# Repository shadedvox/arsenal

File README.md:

# Arsenal

A 6-DOF robotic arm built around a custom STM32 motor controller, closed-loop steppers, and a distributed ROS control stack. The project moves through four stages: electronics, mechanical build, firmware/control integration, and final assembly with the end effector.

---

## Stage 1 — Voxboard (electronics)

Voxboard is a custom 4-layer PCB motor controller built to drive all six joints of the arm from a single board. It replaces an earlier ESP32 + 28BYJ-48 stepper setup with a proper closed-loop system capable of real position feedback and real-time multi-axis control.

**Core architecture**
- STM32F446RET6 (LQFP64, 180MHz Cortex-M4 with FPU) handles all real-time motor control
- Raspberry Pi 3B+ runs inverse kinematics (ikpy) and talks to the STM32 over UART
- 3x TMC2209 drivers for the NEMA17 motors at roll, pitch, and yaw
- 3x TMC5160 drivers for the NEMA23 motors at elbow, base and shoulder
- 10 to 20:1 cycloidal gearbox on every joint, with an MT6835 absolute magnetic encoder at each gearbox output shaft for true closed-loop position feedback, no homing required on power-up

**Connectivity**
- CAN (for the end-effector node), USB, dual SPI (encoders + TMC5160s), triple UART (TMC2209s + RPi), I2C, SWD for debug

**Power**
- Single 24V input via XT60, reverse-polarity and surge protected, stepped down to 5V (buck) and 3.3V (LDO) for logic
- USB VBUS backup path with ideal-diode OR-ing, so the board can run off USB power alone for debug/bring-up

**Project Files & Schematics :** [\Stage1 - STM\voxboard](https://github.com/shadedvox/arsenal/tree/main/Stage1%20-%20STM/voxboard)

**Status: design completed - fabrication pending**

---

## Stage 2 — Mechanical build

3D-printed cycloidal gearboxes and joint assemblies, structural frame for the arm.

**Status: in progress**

---

## Stage 3 — Firmware & control

Real-time motor control on the STM32, distributed ROS architecture with MoveIt running on the Pi/PC side.

**Status: in progress**

---

## Stage 4 — Integration & end effector

Final assembly, end-effector design, and full-arm bring-up.

**Status: in progress**

---

*© 2026 Atharva Chauhan, Vox*

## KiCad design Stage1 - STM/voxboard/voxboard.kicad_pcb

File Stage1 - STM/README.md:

# Voxboard

A custom 4-layer motor controller board for a 6-DOF robotic arm, built around an STM32F446RET6. It drives six stepper motors with closed-loop magnetic encoder feedback, talks to a Raspberry Pi for inverse kinematics, and exposes CAN, I2C, and USB for future expansion.

---

## Core MCU

- STM32F446RET6, Cortex-M4 running at 180MHz off an 8MHz crystal
- Standard ST decoupling scheme on VDD/VBAT and VDDA, per-pin 100nF caps plus bulk capacitors
- NRST push button (internal pull-up, no external needed) and a BOOT0 slide switch
- 5-pin SWD header for programming via ST-Link
- Heartbeat LED for status indication

---

## Power

24V enters through an XT60 connector and feeds a back-EMF and filtering network before splitting off to the motors directly. A buck converter (TPS54331) steps 24V down to 5V, feeding an LDO that regulates the final 3.3V logic rail. Running two stages instead of a single 24V-to-3.3V converter keeps the logic rail clean and low-noise.

A P-MOSFET and Schottky diode pair handles priority between the buck output and USB VBUS, so the board always runs off the battery when it's present and only falls back to USB power for programming when it isn't.

Status LEDs indicate activity on each rail: red for 24V, yellow for VBUS/5V, yellow-green for 3.3V.

---

## Motor drivers

Six motors in total: three NEMA17s (roll, pitch, yaw) driven by TMC2209s over single-wire half-duplex UART, and three NEMA23s (base, shoulder, elbow) driven by TMC5160s over a shared SPI bus. The NEMA23s sit at the joints carrying the highest load.

Each TMC2209 gets an address set through its MS1/MS2 pins, allowing multiple drivers to share one UART line. STEP, DIR, and EN are wired per driver, with series resistors for current limiting. DIAG is only connected on the TMC5160s, since those joints need it most and GPIO budget is tight.

Motors connect through JST-XH connectors mounted directly on the board.

---

## Encoders

Six MT6835 magnetic encoders, one per joint, provide absolute position feedback at the gearbox output shaft. They share a single SPI bus. CAL_EN is tied to ground since calibration is triggered through software instead.

---

## CAN bus

An SN65HVD230DR transceiver gives the board a CAN interface, mainly intended for connecting an end-effector controller later on. Includes end-termination and ESD protection placed right at the connector.

---

## I2C

A couple of JST-GH connectors broken out for I2C, left open for future sensors. Same ESD protection approach as the rest of the board's external connectors.

---

## USB

A USB-C 2.0 connector with ESD protection on the D+/D- lines, used purely for programming and debug, not for powering the whole system under normal operation.

---

## ESD protection

Connectors that reach off-board (USB-C, CAN, RPi UART, I2C) get ESD protection right at the connector, stopping any transient before it reaches the rest of the circuit. Buses that stay entirely on-board (encoder SPI, driver SPI, TMC2209 UART) get their ESD protection near the MCU instead, guarding the chip pins directly.

---

## Layout and routing

4-layer stackup: signal, ground, 3.3V power, signal. The ground plane is a single unified pour, motors and logic share it, with noise managed through tight decoupling and via stitching rather than a split plane.

High-current traces run as fill zones rather than individually routed tracks, since a shaped pour handles current distribution far more cleanly for the 24V rail. All vias are standard through-hole, 0.4/0.3mm, chosen as JLCPCB's smallest reliably manufacturable size.

Ground stitching vias run alongside every high-speed signal via to keep return paths short and reduce EMI.

---

## Final board

Custom 3D models were made in Fusion 360 for parts without existing KiCad models, including the main inductor and the motor driver modules. Silkscreen on the back carries a short board description, designer credit, and a small logo.

---

## BOM

Parts list exported from KiCad and matched to JLCPCB part numbers. Total parts cost as of October 2026: **$263.61 for 2 PCBAs** (excludes PCB fabrication and assembly charges). Full BOM and schematic files live in [`/Stage1 - STM`](https://github.com/shadedvox/arsenal/tree/main/Stage1%20-%20STM).

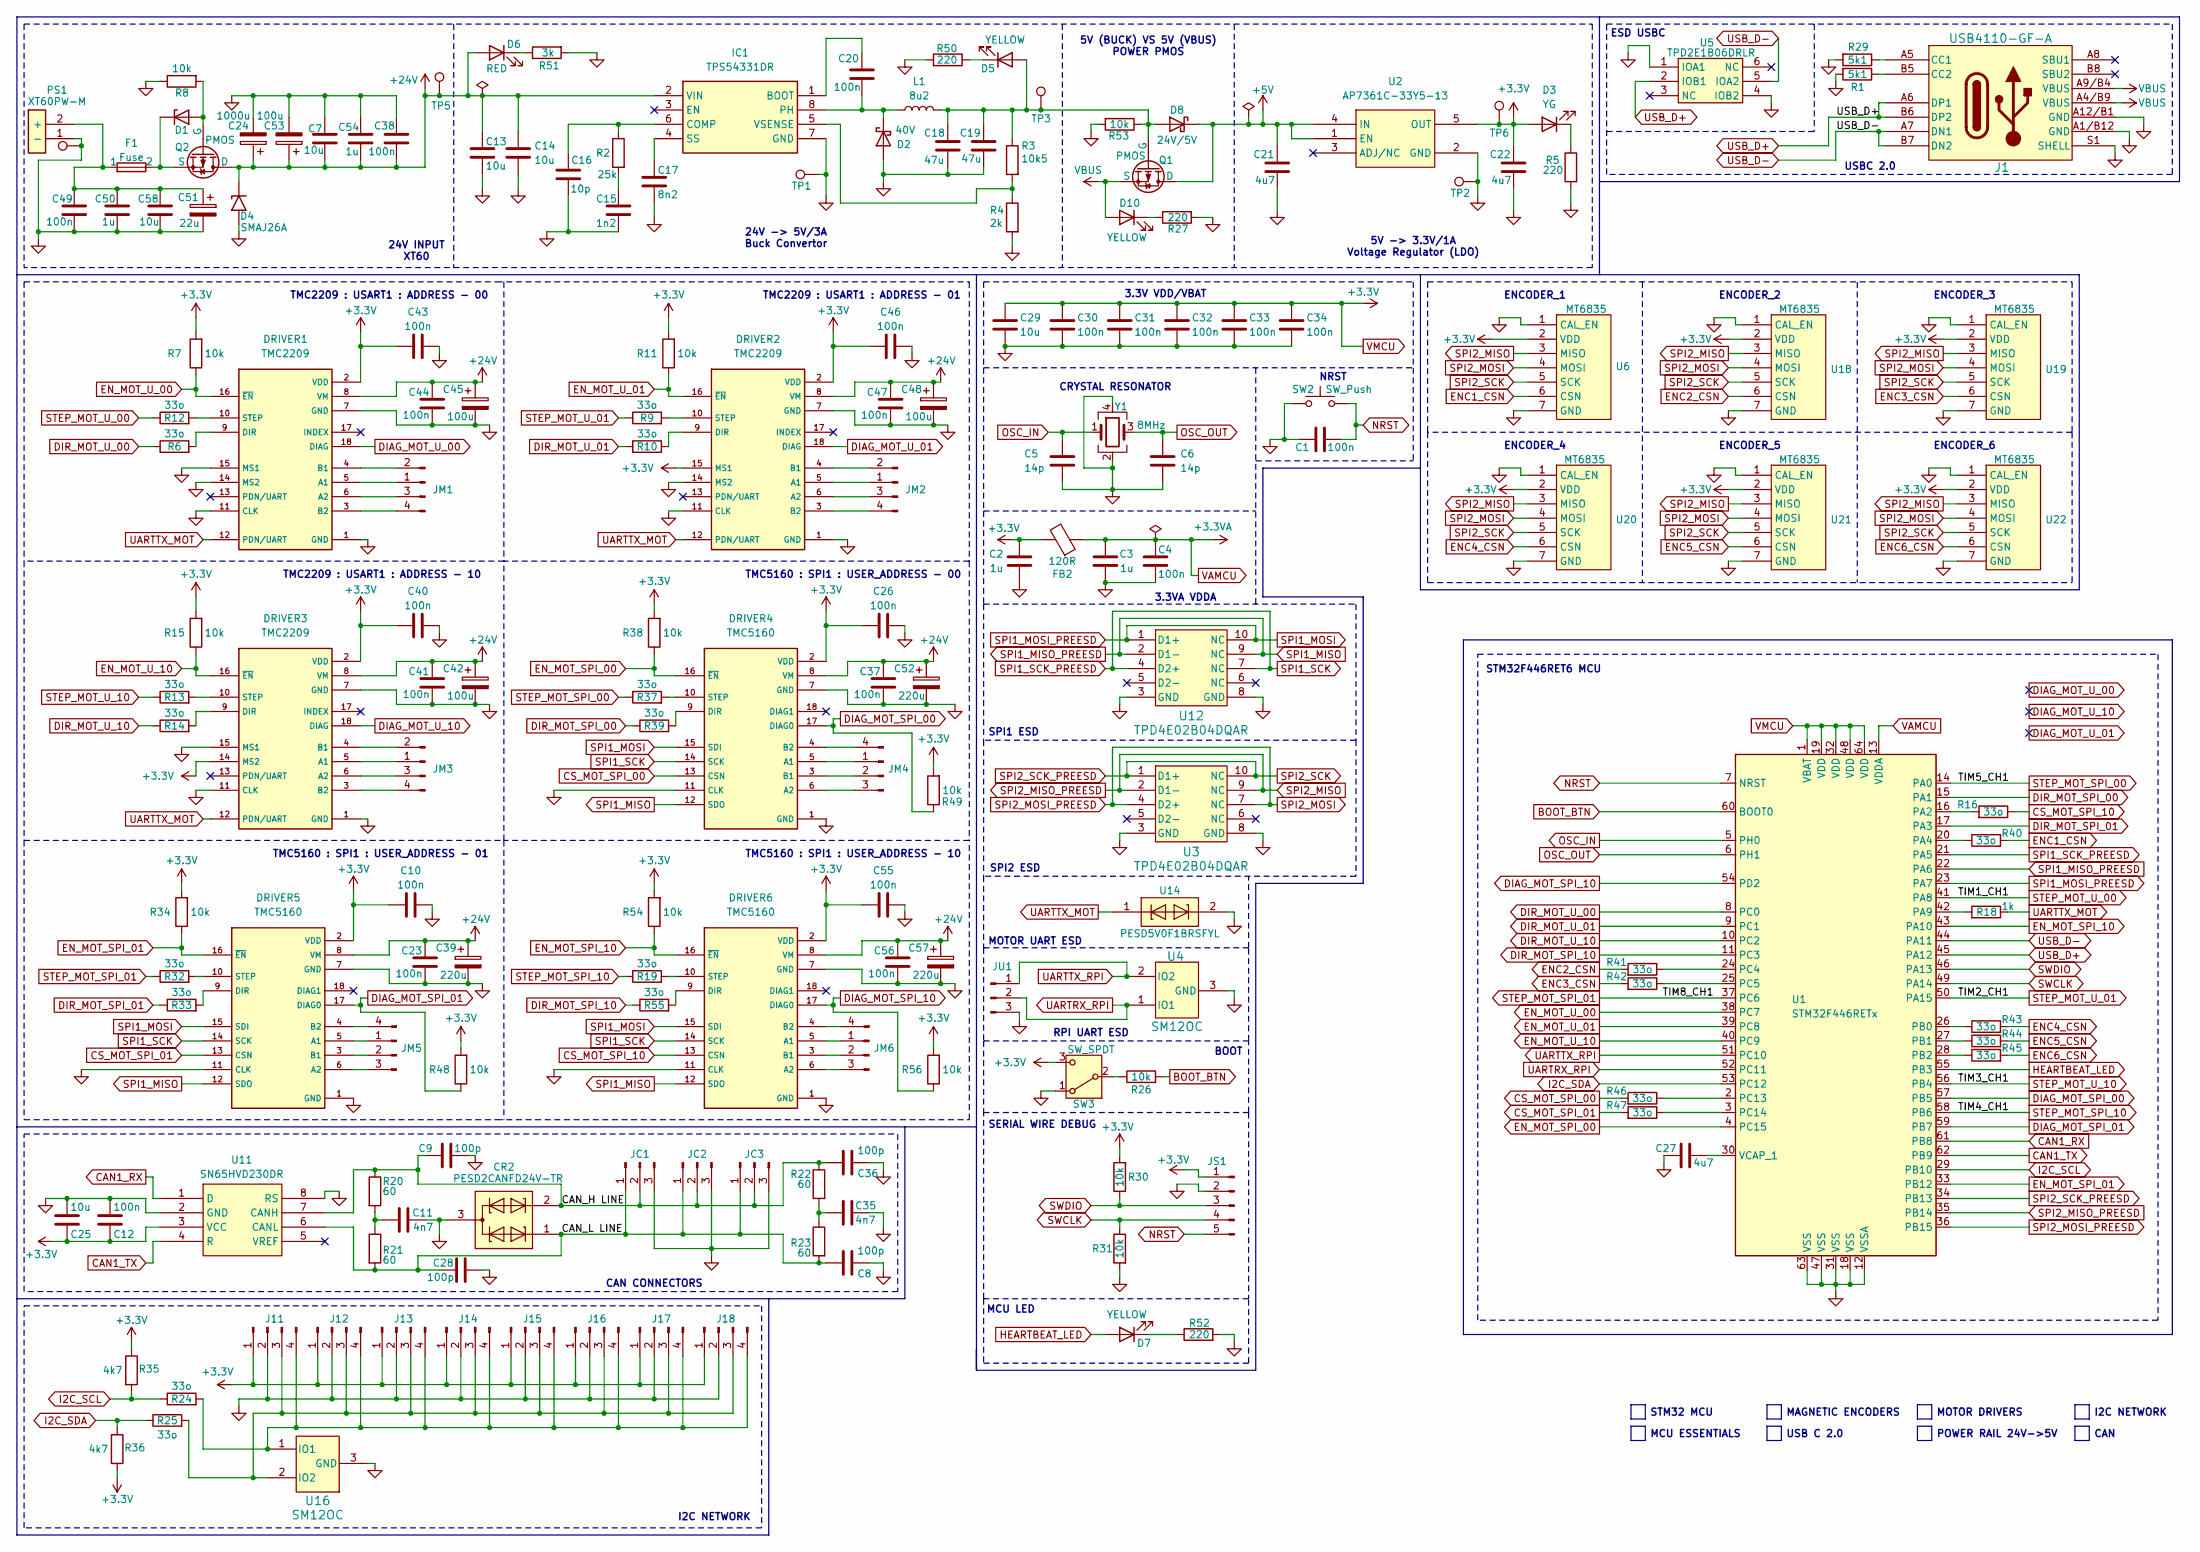
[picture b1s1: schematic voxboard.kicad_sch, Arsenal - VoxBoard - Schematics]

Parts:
C1, C4, C10, C12, C23, C26, C30, C31, C32, C33, C34, C37, C38, C40, C41, C43, C44, C46, C47, C49, C55, C56: 100n; C_0402_1005Metric
C2, C3, C50, C54: 1u; C_0603_1608Metric
C5, C6: 14p; C_0402_1005Metric
C7, C25, C29, C58: 10u; C_0805_2012Metric
C8, C9, C28, C36: 100p; C_0402_1005Metric
C11, C35: 4n7; C_0402_1005Metric
C13, C14: 10u; C_1210_3225Metric
C15: 1n2; C_0805_2012Metric
C16: 10p; C_0805_2012Metric
C17: 8n2; C_0201_0603Metric
C18, C19: 47u; C_1210_3225Metric
C20: 100n; C_0805_2012Metric
C21, C22, C27: 4u7; C_0603_1608Metric
C24: 1000u; CP_Radial_D12.5mm_P5.00mm
C39, C52, C57: 220u; CP_Radial_D10.0mm_P5.00mm
C42, C45, C48: 100u; CP_Radial_D8.0mm_P3.50mm
C51: 22u; CP_Radial_D5.0mm_P2.00mm
C53: 100u; CP_Radial_D6.3mm_P2.50mm
CR2: PESD2CANFD24V-TR; SOT-23
D1: D_Zener; D_SOD-123
D2: 40V; D_SMC
D3: YG; LED_0603_1608Metric
D4: SMAJ26A; D_SMA
D5, D10: YELLOW; LED_0603_1608Metric
D6: RED; LED_0603_1608Metric
D7: YELLOW; LED_0805_2012Metric
D8: 24V/5V; SOT-23
DRIVER1, DRIVER2, DRIVER3: TMC2209; MODULE_TMC2209_5160
DRIVER4, DRIVER5, DRIVER6: TMC5160; MODULE_TMC2209_5160
F1: Fuse; CONN_3557-2_KEY
FB2: 120R; L_0603_1608Metric
IC1: TPS54331DR; SOIC-8_3.9x4.9mm_P1.27mm
J1: USB4110-GF-A; USB_C_Receptacle_GCT_USB4110
J11, J12, J13, J14, J15, J16, J17, J18: Conn_01x04_Pin; JST_GH_BM04B-GHS-TBT_1x04-1MP_P1.25mm_Vertical
JC1, JC2, JC3: Conn_01x03_Pin; JST_GH_BM03B-GHS-TBT_1x03-1MP_P1.25mm_Vertical
JM1, JM2, JM3, JM4, JM5, JM6: Conn_01x04_Pin; JST_XA_B04B-XASK-1_1x04_P2.50mm_Vertical
JS1: Conn_01x05_Pin; PinHeader_1x05_P2.54mm_Vertical
JU1: Conn_01x03_Pin; PinHeader_1x03_P2.54mm_Vertical
L1: 8u2; L_KOHERELEC_MDA7050_7.3x6.6mm
PS1: XT60PW-M; AMASS_XT60PW-M_1x02_P7.20mm_Horizontal
Q1: PMOS; SOT-23
Q2: PMOS; TO-252-2
R1, R29: 5k1; R_0402_1005Metric
R2: 25k; R_0603_1608Metric
R3: 10k5; R_0402_1005Metric
R4: 2k; R_0402_1005Metric
R5, R27, R50, R52: 220; R_0402_1005Metric
R6, R9, R10, R12, R13, R14, R16, R19, R24, R25, R32, R33, R37, R39, R40, R41, R42, R43, R44, R45, R46, R47, R55: 33o; R_0402_1005Metric
R7, R8, R11, R15, R26, R30, R31, R34, R38, R48, R49, R53, R54, R56: 10k; R_0402_1005Metric
R18: 1k; R_0402_1005Metric
R20, R21, R22, R23: 60; R_0603_1608Metric
R35, R36: 4k7; R_0402_1005Metric
R51: 3k; R_0402_1005Metric
SW2: SW_Push; SW_PUSH_B3U-1000PM
SW3: SW_SPDT; SW_SPDT_PCM12
TP1, TP2, TP4: TestPoint; TestPoint_Pad_2.0x2.0mm
TP3, TP5, TP6: TestPoint; TestPoint_Pad_D2.0mm
U1: STM32F446RETx; LQFP64-10x10mm
U2: AP7361C-33Y5-13; AP7361C-33Y5-13_SOT89-5_DIO
U3, U12: TPD4E02B04DQAR; USON-10_2.5x1.0mm_P0.5mm
U4, U16: SM12OC; SOT-23
U5: TPD2E1B06DRLR; SOT-666
U6, U18, U19, U20, U21, U22: MT6835; JST_GH_BM07B-GHS-TBT_1x07-1MP_P1.25mm_Vertical
U11: SN65HVD230DR; SOIC-8_3.9x4.9mm_P1.27mm
U14: PESD5V0F1BRSFYL; Nexperia_DSN0603-2_0.6x0.3mm_P0.4mm
Y1: 8MHz; Crystal_SMD_3225-4Pin_3.2x2.5mm

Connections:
+5V: C21.1, D8.1 (K), Q1.1 (D), U2.1 (EN), U2.4 (IN)
+24V: C7.2, C13.1, C14.1, C23.1, C24.1, C37.1, C38.2, C39.1, C41.1, C42.1, C44.1, C45.1, C47.1, C48.1, C52.1, C53.1, C54.2, C56.1, C57.1, D4.1 (A1), D6.2 (A), DRIVER1.8 (VM), DRIVER2.8 (VM), DRIVER3.8 (VM), DRIVER4.8 (VM), DRIVER5.8 (VM), DRIVER6.8 (VM), IC1.2 (VIN), Q2.1 (D), TP5.1
/CAN_H LINE: C9.1, C36.1, CR2.2, JC1.2, JC2.2, JC3.2, R20.1, R22.1, U11.7 (CANH)
/CAN_L LINE: C8.1, C28.1, CR2.1, JC1.1, JC2.1, JC3.1, R21.2, R23.2, U11.6 (CANL)
BOOT_BTN: R26.2, U1.60 (BOOT0)
CAN1_RX: U1.61 (PB8), U11.1 (D)
CAN1_TX: U1.62 (PB9), U11.4 (R)
CS_MOT_SPI_00: DRIVER4.13 (CSN), R46.2
CS_MOT_SPI_01: DRIVER5.13 (CSN), R47.2
CS_MOT_SPI_10: DRIVER6.13 (CSN), R16.1
DIAG_MOT_SPI_00: DRIVER4.17 (DIAG0), R49.1, U1.57 (PB5)
DIAG_MOT_SPI_01: DRIVER5.17 (DIAG0), R48.1, U1.59 (PB7)
DIAG_MOT_SPI_10: DRIVER6.17 (DIAG0), R56.1, U1.54 (PD2)
DIAG_MOT_U_00: DRIVER1.18 (DIAG)
DIAG_MOT_U_01: DRIVER2.18 (DIAG)
DIAG_MOT_U_10: DRIVER3.18 (DIAG)
DIR_MOT_SPI_00: R39.1, U1.15 (PA1)
DIR_MOT_SPI_01: R33.1, U1.17 (PA3)
DIR_MOT_SPI_10: R55.1, U1.11 (PC3)
DIR_MOT_U_00: R6.1, U1.8 (PC0)
DIR_MOT_U_01: R10.1, U1.9 (PC1)
DIR_MOT_U_10: R14.1, U1.10 (PC2)
ENC1_CSN: R40.2, U6.6 (CSN)
ENC2_CSN: R41.2, U18.6 (CSN)
ENC3_CSN: R42.2, U19.6 (CSN)
ENC4_CSN: R43.2, U20.6 (CSN)
ENC5_CSN: R44.2, U21.6 (CSN)
ENC6_CSN: R45.2, U22.6 (CSN)
EN_MOT_SPI_00: DRIVER4.16 (~EN), R38.1, U1.4 (PC15)
EN_MOT_SPI_01: DRIVER5.16 (~EN), R34.1, U1.33 (PB12)
EN_MOT_SPI_10: DRIVER6.16 (~EN), R54.1, U1.43 (PA10)
EN_MOT_U_00: DRIVER1.16 (~EN), R7.1, U1.38 (PC7)
EN_MOT_U_01: DRIVER2.16 (~EN), R11.1, U1.39 (PC8)
EN_MOT_U_10: DRIVER3.16 (~EN), R15.1, U1.40 (PC9)
GND: C1.1, C2.2, C3.2, C4.2, C5.2, C6.2, C7.1, C8.2, C9.2, C10.2, C11.2, C12.2, C13.2, C14.2, C15.2, C16.2, C17.2, C18.2, C19.2, C21.2, C22.2, C23.2, C24.2, C25.2, C26.2, C27.1, C28.2, C29.2, C30.2, C31.2, C32.2, C33.2, C34.2, C35.2, C36.2, C37.2, C38.1, C39.2, C40.2, C41.2, C42.2, C43.2, C44.2, C45.2, C46.2, C47.2, C48.2, C49.2, C50.2, C51.2, C52.2, C53.2, C54.1, C55.2, C56.2, C57.2, C58.2, CR2.3, D2.2 (A), D4.2 (A2), DRIVER1.1 (GND), DRIVER1.7 (GND), DRIVER1.11 (CLK), DRIVER1.14 (MS2), DRIVER1.15 (MS1), DRIVER2.1 (GND), DRIVER2.7 (GND), DRIVER2.11 (CLK), DRIVER2.14 (MS2), DRIVER3.1 (GND), DRIVER3.7 (GND), DRIVER3.11 (CLK), DRIVER3.15 (MS1), DRIVER4.1 (GND), DRIVER4.7 (GND), DRIVER4.11 (CLK), DRIVER5.1 (GND), DRIVER5.7 (GND), DRIVER5.11 (CLK), DRIVER6.1 (GND), DRIVER6.7 (GND), DRIVER6.11 (CLK), IC1.7 (GND), J1.A1/B12 (GND), J1.A12/B1 (GND), J1.S1 (SHELL), J11.2, J12.2, J13.2, J14.2, J15.2, J16.2, J17.2, J18.2, JC1.3, JC2.3, JC3.3, JS1.2, JU1.3, PS1.1 (-), R1.2, R4.2, R5.2, R8.1, R27.2, R29.2, R31.2, R50.2, R51.2, R52.2, R53.2, SW2.1, SW3.1 (A), TP1.1, TP2.1, TP4.1, U1.12 (VSSA), U1.18 (VSS), U1.31 (VSS), U1.47 (VSS), U1.63 (VSS), U2.2 (GND), U3.3 (GND), U3.8 (GND), U4.3 (GND), U5.1 (IOA1), U5.4 (IOB2), U6.1 (CAL_EN), U6.7 (GND), U11.2 (GND), U11.8 (RS), U12.3 (GND), U12.8 (GND), U14.2, U16.3 (GND), U18.1 (CAL_EN), U18.7 (GND), U19.1 (CAL_EN), U19.7 (GND), U20.1 (CAL_EN), U20.7 (GND), U21.1 (CAL_EN), U21.7 (GND), U22.1 (CAL_EN), U22.7 (GND), Y1.2 (G), Y1.4 (G)
HEARTBEAT_LED: D7.2 (A), U1.55 (PB3)
I2C_SCL: R24.1, R35.2, U1.29 (PB10)
I2C_SDA: R25.1, R36.1, U1.53 (PC12)
NRST: C1.2, JS1.5, SW2.2, U1.7 (NRST)
unnamed: C11.1, R20.2, R21.1
unnamed: C15.1, R2.2
unnamed: C35.1, R22.2, R23.1
unnamed: D1.2 (A), Q2.2 (G), R8.2
unnamed: D1.1 (K), F1.2, Q2.3 (S)
unnamed: C20.2, D2.1 (K), IC1.8 (PH), L1.1
unnamed: D3.1 (K), R5.1
unnamed: C18.1, C19.1, D5.2 (A), D8.2 (A), L1.2, Q1.2 (G), R3.1, R53.1, TP3.1
unnamed: D5.1 (K), R50.1
unnamed: D6.1 (K), R51.1
unnamed: D7.1 (K), R52.1
unnamed: D10.1 (K), R27.1
unnamed: DRIVER1.5 (A1), JM1.1
unnamed: DRIVER1.6 (A2), JM1.3
unnamed: DRIVER1.4 (B1), JM1.2
unnamed: DRIVER1.3 (B2), JM1.4
unnamed: DRIVER1.9 (DIR), R6.2
unnamed: DRIVER1.10 (STEP), R12.2
unnamed: DRIVER2.5 (A1), JM2.1
unnamed: DRIVER2.6 (A2), JM2.3
unnamed: DRIVER2.4 (B1), JM2.2
unnamed: DRIVER2.3 (B2), JM2.4
unnamed: DRIVER2.9 (DIR), R10.2
unnamed: DRIVER2.10 (STEP), R9.2
unnamed: DRIVER3.5 (A1), JM3.1
unnamed: DRIVER3.6 (A2), JM3.3
unnamed: DRIVER3.4 (B1), JM3.2
unnamed: DRIVER3.3 (B2), JM3.4
unnamed: DRIVER3.9 (DIR), R14.2
unnamed: DRIVER3.10 (STEP), R13.2
unnamed: DRIVER4.5 (A1), JM4.1
unnamed: DRIVER4.6 (A2), JM4.3
unnamed: DRIVER4.3 (B1), JM4.2
unnamed: DRIVER4.4 (B2), JM4.4
unnamed: DRIVER4.9 (DIR), R39.2
unnamed: DRIVER4.10 (STEP), R37.2
unnamed: DRIVER5.5 (A1), JM5.1
unnamed: DRIVER5.6 (A2), JM5.3
unnamed: DRIVER5.3 (B1), JM5.2
unnamed: DRIVER5.4 (B2), JM5.4
unnamed: DRIVER5.9 (DIR), R33.2
unnamed: DRIVER5.10 (STEP), R32.2
unnamed: DRIVER6.5 (A1), JM6.1
unnamed: DRIVER6.6 (A2), JM6.3
unnamed: DRIVER6.3 (B1), JM6.2
unnamed: DRIVER6.4 (B2), JM6.4
unnamed: DRIVER6.9 (DIR), R55.2
unnamed: DRIVER6.10 (STEP), R19.2
unnamed: C20.1, IC1.1 (BOOT)
unnamed: C16.1, IC1.6 (COMP), R2.1
unnamed: C17.1, IC1.4 (SS)
unnamed: IC1.5 (VSENSE), R3.2, R4.1
unnamed: J1.A5 (CC1), R29.1
unnamed: J1.B5 (CC2), R1.1
unnamed: J11.3, J12.3, J13.3, J14.3, J15.3, J16.3, J17.3, J18.3, R25.2, U16.2 (IO2)
unnamed: J11.4, J12.4, J13.4, J14.4, J15.4, J16.4, J17.4, J18.4, R24.2, U16.1 (IO1)
unnamed: C49.1, C50.1, C51.1, C58.1, F1.1, PS1.2 (+)
unnamed: R26.1, SW3.2 (B)
unnamed: R16.2, U1.16 (PA2)
unnamed: R40.1, U1.20 (PA4)
unnamed: R18.2, U1.42 (PA9)
unnamed: R43.1, U1.26 (PB0)
unnamed: R44.1, U1.27 (PB1)
unnamed: R45.1, U1.28 (PB2)
unnamed: R41.1, U1.24 (PC4)
unnamed: R42.1, U1.25 (PC5)
unnamed: R46.1, U1.2 (PC13)
unnamed: R47.1, U1.3 (PC14)
unnamed: C27.2, U1.30 (VCAP_1)
OSC_IN: C5.1, U1.5 (PH0), Y1.1
OSC_OUT: C6.1, U1.6 (PH1), Y1.3
SPI1_MISO: DRIVER4.12 (SDO), DRIVER5.12 (SDO), DRIVER6.12 (SDO), U1.22 (PA6), U12.2 (D1-), U12.9 (NC)
SPI1_MOSI: DRIVER4.15 (SDI), DRIVER5.15 (SDI), DRIVER6.15 (SDI), U1.23 (PA7), U12.1 (D1+), U12.10 (NC)
SPI1_SCK: DRIVER4.14 (SCK), DRIVER5.14 (SCK), DRIVER6.14 (SCK), U1.21 (PA5), U12.4 (D2+), U12.7 (NC)
SPI2_MISO: U1.35 (PB14), U3.2 (D1-), U3.9 (NC), U6.3 (MISO), U18.3 (MISO), U19.3 (MISO), U20.3 (MISO), U21.3 (MISO), U22.3 (MISO)
SPI2_MOSI: U1.36 (PB15), U3.4 (D2+), U3.7 (NC), U6.4 (MOSI), U18.4 (MOSI), U19.4 (MOSI), U20.4 (MOSI), U21.4 (MOSI), U22.4 (MOSI)
SPI2_SCK: U1.34 (PB13), U3.1 (D1+), U3.10 (NC), U6.5 (SCK), U18.5 (SCK), U19.5 (SCK), U20.5 (SCK), U21.5 (SCK), U22.5 (SCK)
STEP_MOT_SPI_00: R37.1, U1.14 (PA0)
STEP_MOT_SPI_01: R32.1, U1.37 (PC6)
STEP_MOT_SPI_10: R19.1, U1.58 (PB6)
STEP_MOT_U_00: R12.1, U1.41 (PA8)
STEP_MOT_U_01: R9.1, U1.50 (PA15)
STEP_MOT_U_10: R13.1, U1.56 (PB4)
SWCLK: JS1.4, R31.1, U1.49 (PA14)
SWDIO: JS1.3, R30.1, U1.46 (PA13)
UARTRX_RPI: JU1.2, U1.52 (PC11), U4.1 (IO1)
UARTTX_MOT: DRIVER1.12 (PDN/UART), DRIVER2.12 (PDN/UART), DRIVER3.12 (PDN/UART), R18.1, U14.1
UARTTX_RPI: JU1.1, U1.51 (PC10), U4.2 (IO2)
USB_D+: J1.A6 (DP1), J1.B6 (DP2), U1.45 (PA12), U5.2 (IOB1)
USB_D-: J1.A7 (DN1), J1.B7 (DN2), U1.44 (PA11), U5.5 (IOA2)
VAMCU: C3.1, C4.1, FB2.1, U1.13 (VDDA)
VBUS: D10.2 (A), J1.A4/B9 (VBUS), J1.A9/B4 (VBUS), Q1.3 (S)
VMCU: C2.1, C10.1, C12.1, C22.1, C25.1, C26.1, C29.1, C30.1, C31.1, C32.1, C33.1, C34.1, C40.1, C43.1, C46.1, C55.1, D3.2 (A), DRIVER1.2 (VDD), DRIVER2.2 (VDD), DRIVER2.15 (MS1), DRIVER3.2 (VDD), DRIVER3.14 (MS2), DRIVER4.2 (VDD), DRIVER5.2 (VDD), DRIVER6.2 (VDD), FB2.2, J11.1, J12.1, J13.1, J14.1, J15.1, J16.1, J17.1, J18.1, JS1.1, R7.2, R11.2, R15.2, R30.2, R34.2, R35.1, R36.2, R38.2, R48.2, R49.2, R54.2, R56.2, SW3.3 (C), TP6.1, U1.1 (VBAT), U1.19 (VDD), U1.32 (VDD), U1.48 (VDD), U1.64 (VDD), U2.5 (OUT), U6.2 (VDD), U11.3 (VCC), U18.2 (VDD), U19.2 (VDD), U20.2 (VDD), U21.2 (VDD), U22.2 (VDD)

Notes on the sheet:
ESD USBC
TMC5160 : SPI1 : USER_ADDRESS - 10
STM32 MCU
NRST
TMC5160 : SPI1 : USER_ADDRESS - 01
ENCODER_4
MOTOR UART ESD
TMC2209 : USART1 : ADDRESS - 10
TMC2209 : USART1 : ADDRESS - 01
ENCODER_6
MOTOR DRIVERS
BOOT
MAGNETIC ENCODERS
RPI UART ESD
3.3V VDD/VBAT
CAN
TMC5160 : SPI1 : USER_ADDRESS - 00
ENCODER_5
CAN CONNECTORS
SPI1 ESD
USBC 2.0
I2C NETWORK
MCU ESSENTIALS
3.3VA VDDA
ENCODER_2
24V -> 5V/3A Buck Convertor
SPI2 ESD
ENCODER_3
USB C 2.0
MCU LED
POWER RAIL 24V->5V
CRYSTAL RESONATOR
SERIAL WIRE DEBUG
STM32F446RET6 MCU
5V -> 3.3V/1A Voltage Regulator (LDO)
TMC2209 : USART1 : ADDRESS - 00
24V INPUT XT60
ENCODER_1
5V (BUCK) VS 5V (VBUS) POWER PMOS

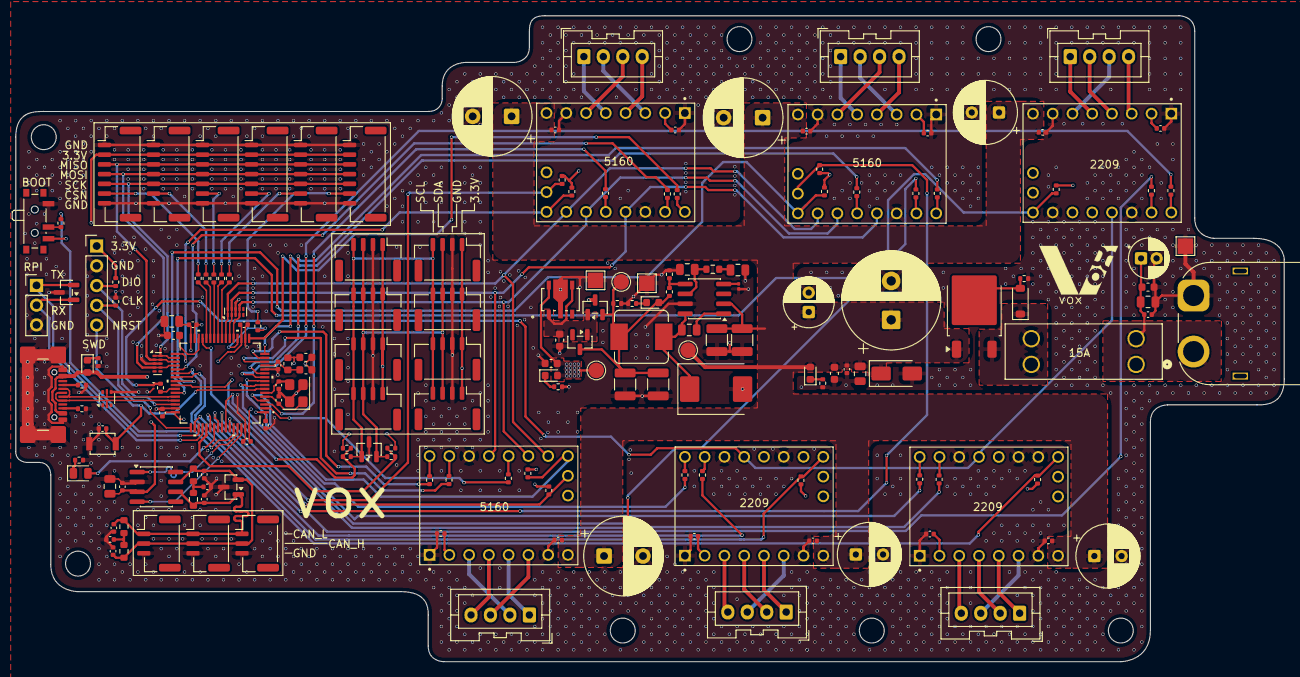
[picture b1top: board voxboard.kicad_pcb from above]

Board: 4 copper layers, 163.0 x 83.0 mm, 179 parts (0 on the bottom side), 129 nets.

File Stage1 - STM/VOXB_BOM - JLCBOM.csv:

Comment,Designator,Footprint,JLCPCB Part#(optional)
100nF,"C1, C10, C12, C23, C26, C30, C31, C32, C33, C34, C37, C38, C4, C40, C41, C43, C44, C46, C47, C49, C55, C56",C0402,C56392
4.7nF,"C11, C35",C0402,C1538
10uF,"C13, C14",C1210,C39232
1.2nF,C15,C0805,C1714
10pF,C16,C0805,C107107
8.2nF,C17,C0201,C2168104
47uF,"C18, C19",C1210,C84494
1uF,"C2, C3, C50, C54",C0603,C29936
100nF,C20,C0805,C1711
4.7uF,"C21, C22, C27",C0603,C69335
1000uF,C24,CP_Radial_D12.5mm_P5.00mm,C165529
10uF,"C25, C29, C58, C7",C0805,C440198
100pF,"C28, C36, C8, C9",C0402,C1546
220uF,"C39, C52, C57",CP_Radial_D10.0mm_P5.00mm,C19270689
100uF,"C42, C45, C48, C53",CP_Radial_D6.3mm_P2.50mm,C19270686
14pF,"C5, C6",C0402,C458857
22uF,C51,CP_Radial_D5.0mm_P2.00mm,C216548
PESD2CANFD24V-TR,CR2,SOT-23,C552486
D_Zener,D1,D_SOD-123,C74710
YELLOW,"D10, D5",D0603,C2287
40V,D2,D_SMC,C72264
YG,D3,D0603,C2289
SMAJ26A,D4,D_SMA,C49370
RED,D6,D0603,C2286
YELLOW,D7,D0805,C2292
24V/5V,D8,SOT-23,C8590
120Ω,FB2,FB0603,C12391
TPS54331DR,IC1,SOIC-8_3.9x4.9mm_P1.27mm,C9865
USB4110-GF-A,J1,USB_C_Receptacle_GCT_USB4110,C5143397
Conn_01x04_Pin,"J11, J12, J13, J14, J15, J16, J17, J18",JST_GH_BM04B-GHS-TBT_1x04-1MP_P1.25mm_Vertical,C161692
Conn_01x03_Pin,"JC1, JC2, JC3",JST_GH_BM03B-GHS-TBT_1x03-1MP_P1.25mm_Vertical,C161691
Conn_01x04_Pin,"JM1, JM2, JM3, JM4, JM5, JM6",JST_XA_B04B-XASK-1_1x04_P2.50mm_Vertical,C264994
8.2uH,L1,L_KOHERELEC_MDA7050_7.3x6.6mm,C5359716
5.1Ω,"R1, R29",R0402,C25905
33Ω,"R10, R12, R13, R14, R16, R19, R24, R25, R32, R33, R37, R39, R40, R41, R42, R43, R44, R45, R46, R47, R55, R6, R9",R0402,C25105
10kΩ,"R11, R15, R26, R30, R31, R34, R38, R48, R49, R53, R54, R56, R7, R8",R0402,C25531
1kΩ,R18,R0402,C11702
25kΩ,R2,R0603,C2828637
60Ω,"R20, R21, R22, R23",R0603,C166918
220Ω,"R27, R5, R50, R52",R0402,C25091
10.5kΩ,R3,R0402,C100202
4.7kΩ,"R35, R36",R0402,C25900
2kΩ,R4,R0402,C4109
3kΩ,R51,R0402,C25784
SW_Push,SW2,SW_PUSH_B3U-1000PM,C231329
SW_SPDT,SW3,SW_SPDT_PCM12,C49023767
STM32F446RETx,U1,LQFP64-10x10mm,C69336
SN65HVD230DR,U11,SOIC-8_3.9x4.9mm_P1.27mm,C12084
TPD4E02B04DQAR,"U12, U3",USON-10_2.5x1.0mm_P0.5mm,C106794
PESD5V0F1BRSFYL,U14,Nexperia_DSN0603-2_0.6x0.3mm_P0.4mm,C552550
SM12OC,"U16, U4",SOT-23,C20417175
MT6835,"U18, U19, U20, U21, U22, U6",JST_GH_BM07B-GHS-TBT_1x07-1MP_P1.25mm_Vertical,C5305068
AP7361C-33Y5-13,U2,AP7361C-33Y5-13_SOT89-5_DIO,C460397
TPD2E1B06DRLR,U5,SOT-666,C1974127
8MHz,Y1,Crystal_SMD_3225-4Pin_3.2x2.5mm,C2933033

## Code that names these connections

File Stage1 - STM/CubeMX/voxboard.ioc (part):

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Mcu.Name=STM32F446R(C-E)Tx
Mcu.Package=LQFP64
Mcu.UserName=STM32F446RETx
PA0-WKUP.Signal=S_TIM5_CH1
PA1.Signal=GPIO_Output
PA10.Signal=GPIO_Output
PA11.Mode=Device_Only
PA11.Signal=USB_OTG_FS_DM
PA12.Mode=Device_Only
PA12.Signal=USB_OTG_FS_DP
PA13.Mode=Serial_Wire
PA13.Signal=SYS_JTMS-SWDIO
PA14.Mode=Serial_Wire
PA14.Signal=SYS_JTCK-SWCLK
PA15.Signal=S_TIM2_CH1_ETR
PA2.Signal=GPIO_Output
PA3.Signal=GPIO_Output
PA4.Signal=GPIO_Output
PA5.Mode=Full_Duplex_Master
PA5.Signal=SPI1_SCK
PA6.Mode=Full_Duplex_Master
PA6.Signal=SPI1_MISO
PA7.Mode=Full_Duplex_Master
PA7.Signal=SPI1_MOSI
PA8.Signal=S_TIM1_CH1
PA9.Mode=Half_duplex(single_wire_mode)
PA9.Signal=USART1_TX
PB0.Signal=GPIO_Output
PB1.Signal=GPIO_Output
PB10.Mode=I2C
PB10.Signal=I2C2_SCL
PB12.Signal=GPIO_Output
PB13.Mode=Full_Duplex_Master
PB13.Signal=SPI2_SCK
PB14.Mode=Full_Duplex_Master
PB14.Signal=SPI2_MISO
PB15.Mode=Full_Duplex_Master
PB15.Signal=SPI2_MOSI
PB2.Signal=GPIO_Output
PB3.Signal=GPIO_Output
PB4.Signal=S_TIM3_CH1
PB5.Signal=GPIO_Input
PB6.Signal=S_TIM4_CH1
PB7.Signal=GPIO_Input
PB8.Mode=CAN_Activate
PB8.Signal=CAN1_RX
PB9.Mode=CAN_Activate
PB9.Signal=CAN1_TX
PC0.Signal=GPIO_Output
PC1.Signal=GPIO_Output
PC10.Mode=Asynchronous
PC10.Signal=USART3_TX
PC11.Mode=Asynchronous
PC11.Signal=USART3_RX
PC12.Mode=I2C
PC12.Signal=I2C2_SDA
PC13.Signal=GPIO_Output
PC14-OSC32_IN.Signal=GPIO_Output
PC15-OSC32_OUT.Signal=GPIO_Output
PC2.Signal=GPIO_Output
PC3.Signal=GPIO_Output
PC4.Signal=GPIO_Output
PC5.Signal=GPIO_Output
PC6.Signal=S_TIM8_CH1
PC7.Signal=GPIO_Output
PC8.Signal=GPIO_Output
PC9.Signal=GPIO_Output
PD2.Signal=GPIO_Input
PH0-OSC_IN.Mode=HSE-External-Oscillator
PH0-OSC_IN.Signal=RCC_OSC_IN
PH1-OSC_OUT.Mode=HSE-External-Oscillator
PH1-OSC_OUT.Signal=RCC_OSC_OUT
RCC.HSE_VALUE=8000000
RCC.SYSCLKFreq_VALUE=180000000
RCC.SYSCLKSource=RCC_SYSCLKSOURCE_PLLCLK
board=custom

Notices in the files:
Stage1 - STM/voxboard/voxboard.kicad_pcb:
Copyright © 2026 Atharva Chauhan. All rights reserved.
